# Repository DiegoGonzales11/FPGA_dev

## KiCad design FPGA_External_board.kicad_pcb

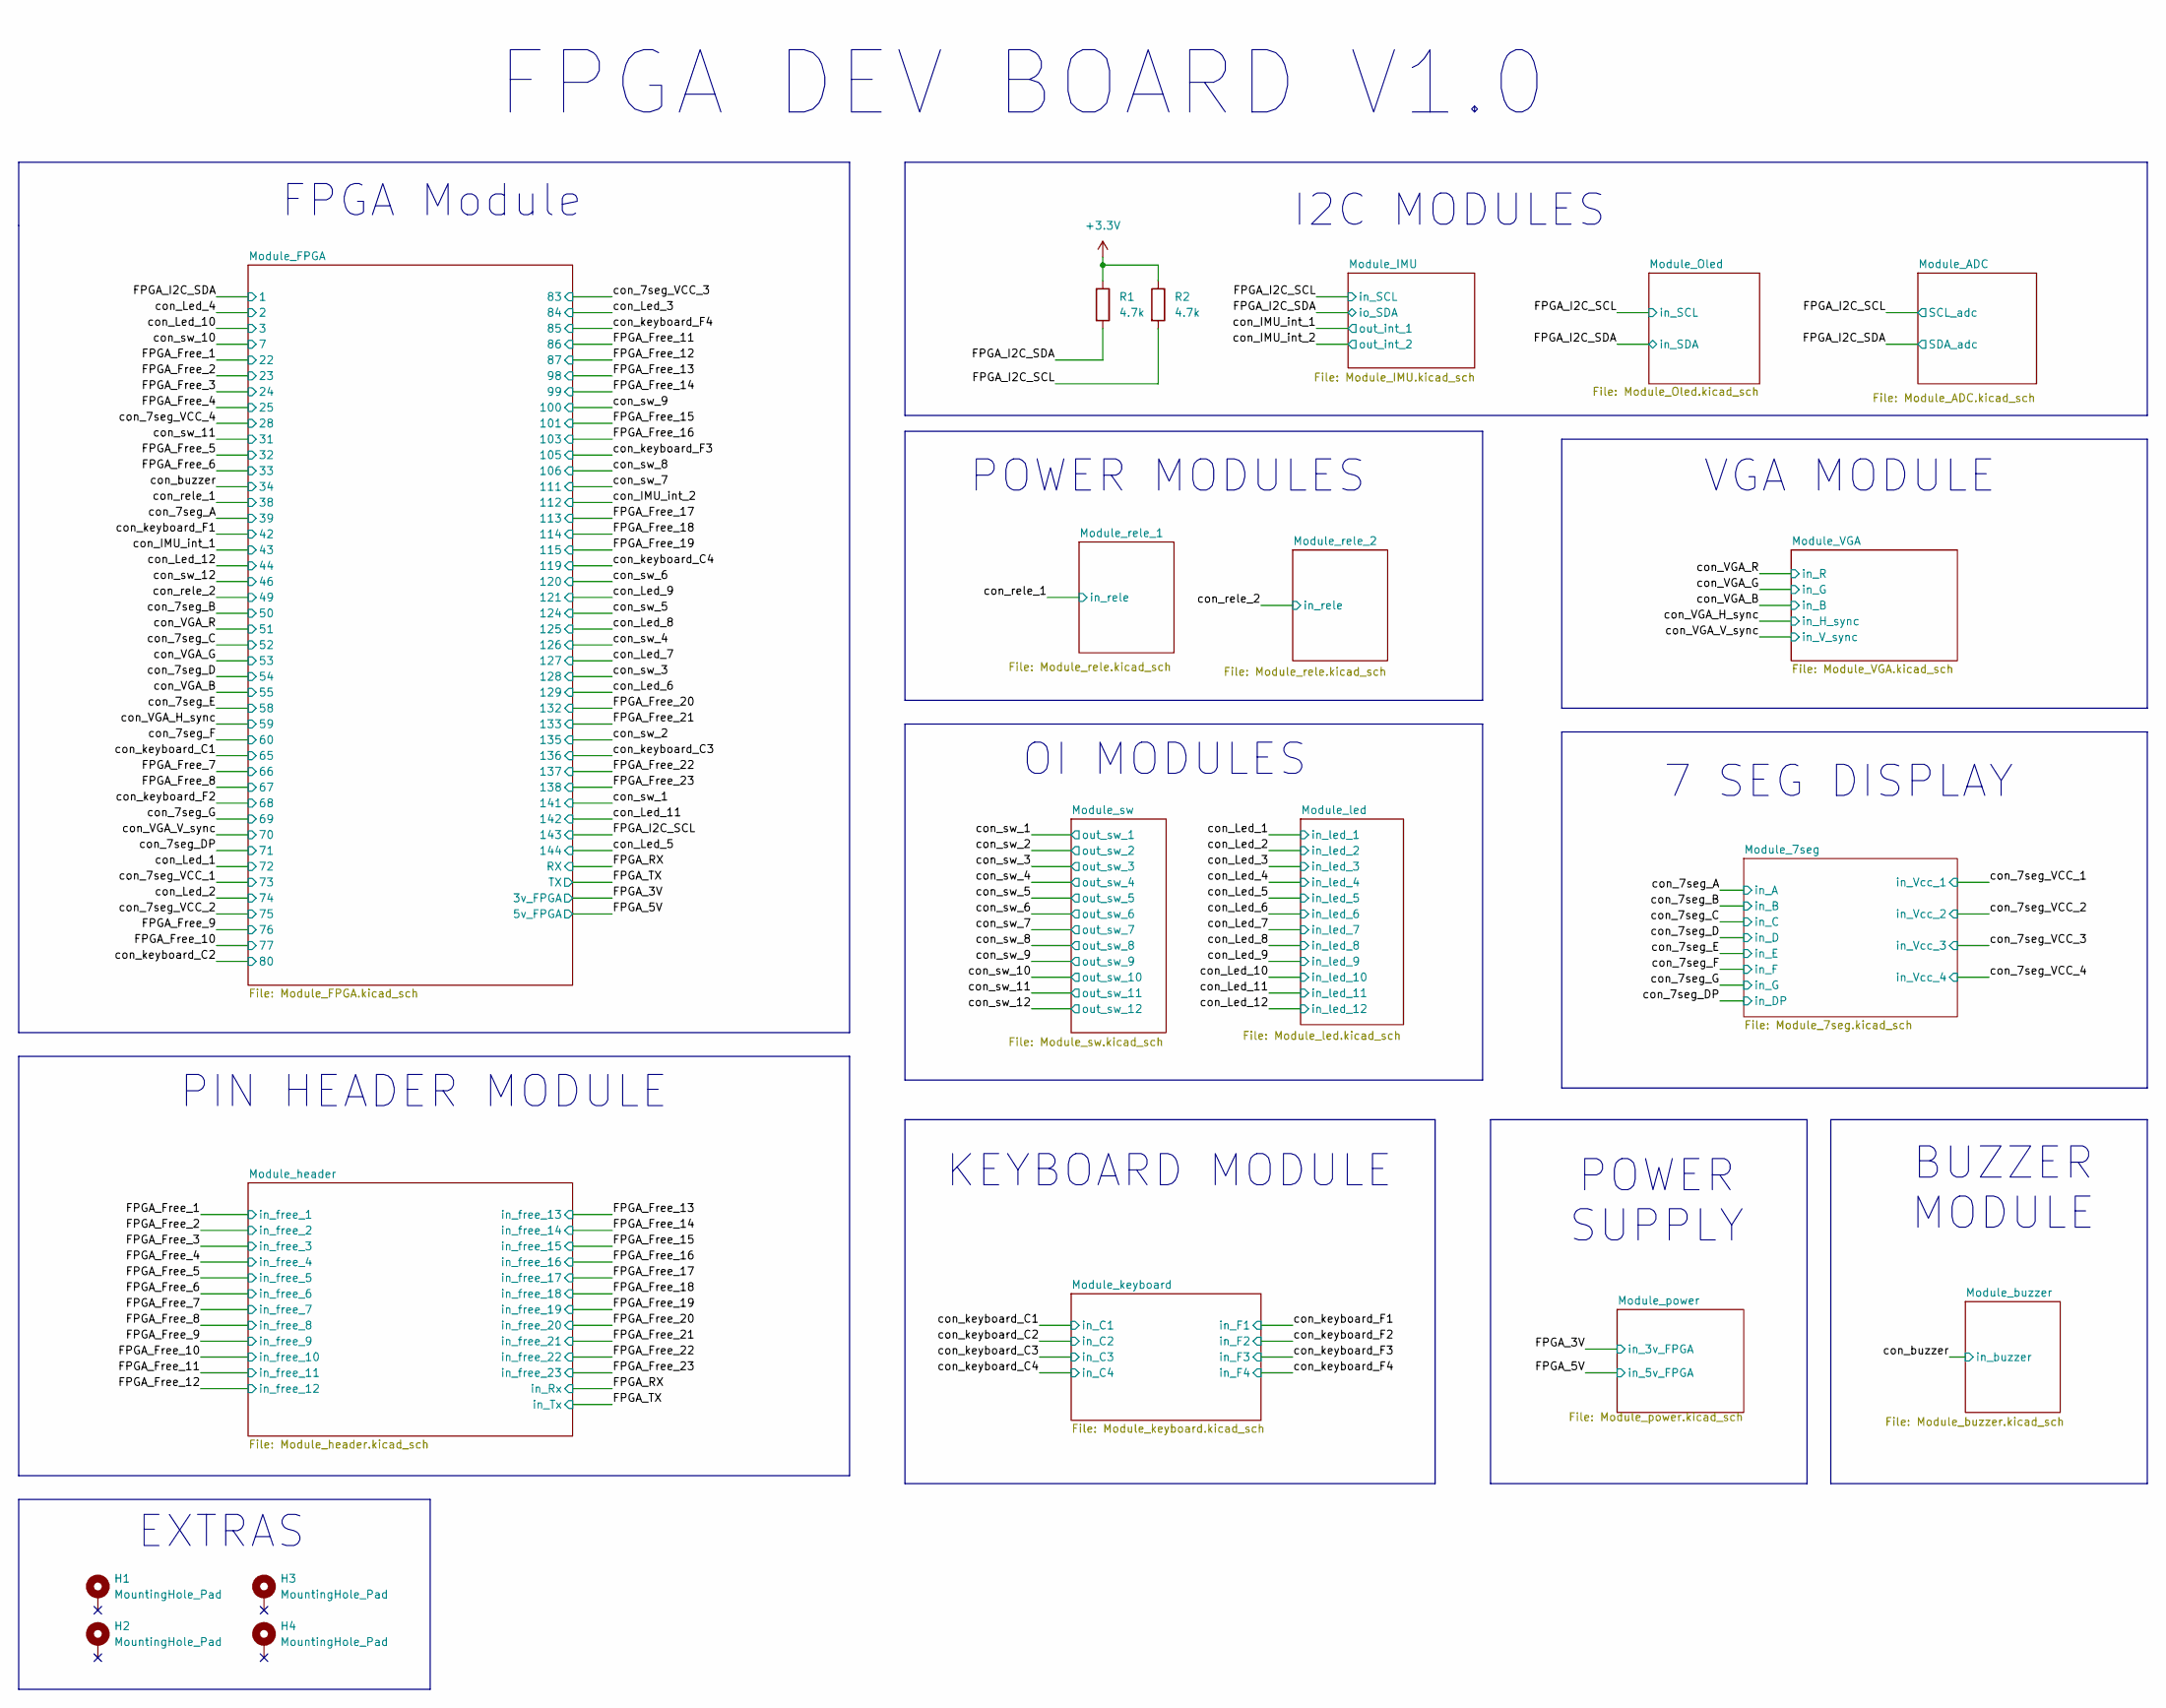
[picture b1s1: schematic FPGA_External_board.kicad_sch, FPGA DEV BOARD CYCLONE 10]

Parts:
H1, H2, H3, H4: MountingHole_Pad; Mounting Hole 3mm
R1, R2: 4.7k; R_0805_2012Metric_Pad1.20x1.40mm_HandSolder

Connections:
+3.3V: R1.1, R2.1; also elsewhere on the board
/FPGA_I2C_SCL: R2.2; also elsewhere on the board
/FPGA_I2C_SDA: R1.2; also elsewhere on the board

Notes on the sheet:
7 SEG DISPLAY
FPGA DEV BOARD V1.0
POWER MODULES
KEYBOARD MODULE
EXTRAS
PIN HEADER MODULE
OI MODULES
FPGA Module
POWER SUPPLY
I2C MODULES
BUZZER MODULE
VGA MODULE

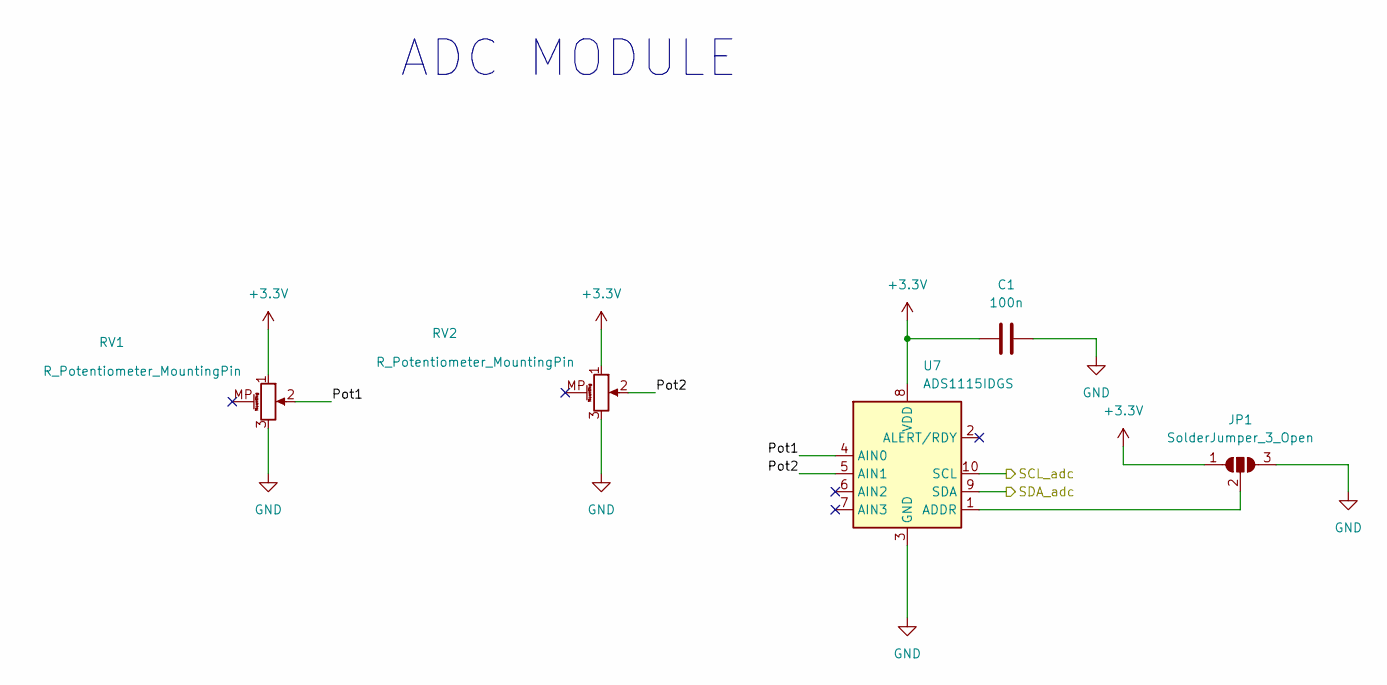
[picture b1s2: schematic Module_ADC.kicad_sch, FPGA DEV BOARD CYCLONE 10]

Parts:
C1: 100n; C_0805_2012Metric
JP1: SolderJumper_3_Open; SolderJumper-3_P1.3mm_Open_RoundedPad1.0x1.5mm
RV1, RV2: R_Potentiometer_MountingPin; Potentiometer_Alps_RK09K_Single_Vertical
U7: ADS1115IDGS; TSSOP-10_3x3mm_P0.5mm

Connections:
+3.3V: C1.2, JP1.1 (A), RV1.1, RV2.1, U7.8 (VDD); also elsewhere on the board
/FPGA_I2C_SCL: U7.10 (SCL); also elsewhere on the board
/FPGA_I2C_SDA: U7.9 (SDA); also elsewhere on the board
/Module_ADC/Pot1: RV1.2, U7.4 (AIN0)
/Module_ADC/Pot2: RV2.2, U7.5 (AIN1)
GND: C1.1, JP1.3 (B), RV1.3, RV2.3, U7.3 (GND); also elsewhere on the board
unnamed: JP1.2 (C), U7.1 (ADDR)

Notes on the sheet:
ADC MODULE

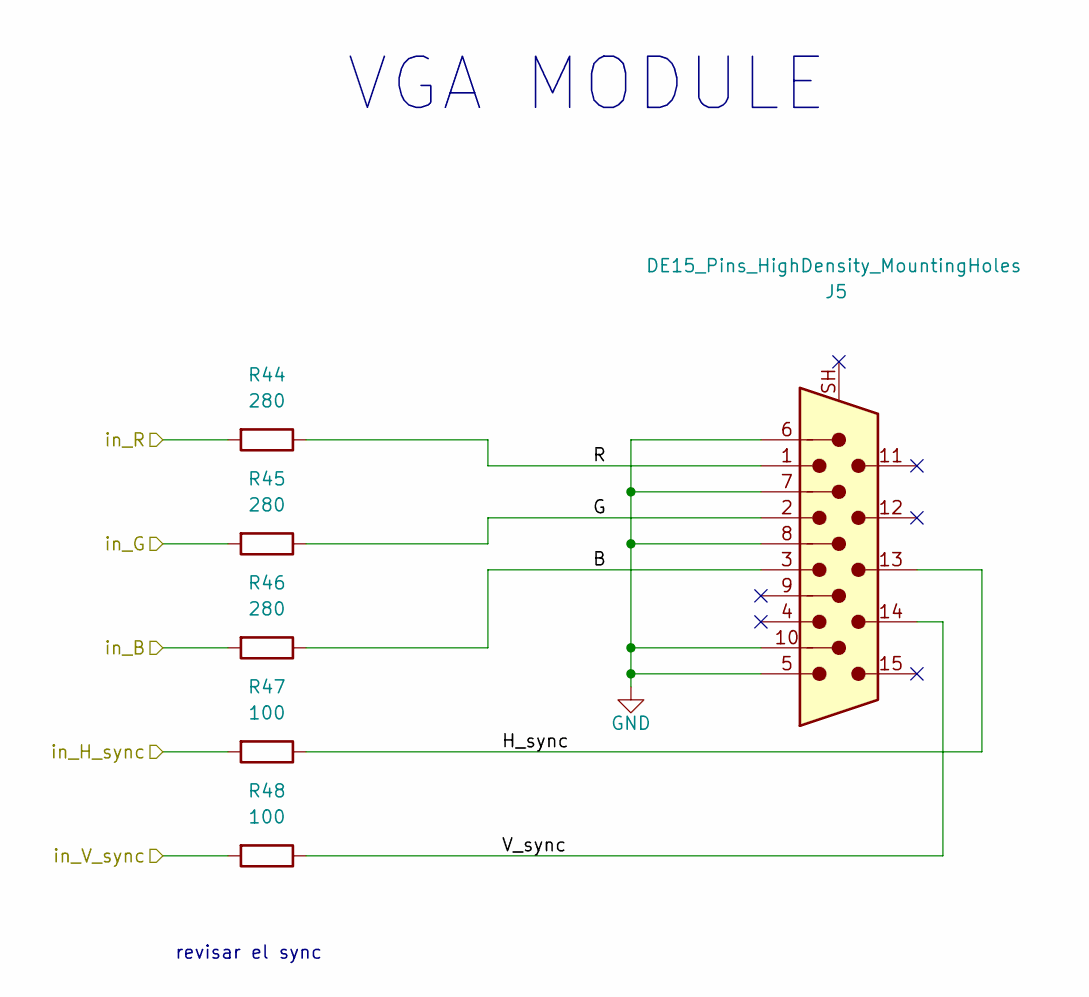
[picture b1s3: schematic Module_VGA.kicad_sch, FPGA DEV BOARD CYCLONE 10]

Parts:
J5: DE15_Pins_HighDensity_MountingHoles; DSUB-15-HD_Pins_Horizontal_P2.29x2.54mm_EdgePinOffset8.35mm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
R44, R45, R46: 280; R_0805_2012Metric_Pad1.20x1.40mm_HandSolder
R47, R48: 100; R_0805_2012Metric_Pad1.20x1.40mm_HandSolder

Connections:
/Module_VGA/B: J5.3, R46.1
/Module_VGA/G: J5.2, R45.1
/Module_VGA/H_sync: J5.13, R47.1
/Module_VGA/R: J5.1, R44.1
/Module_VGA/V_sync: J5.14, R48.1
/con_VGA_B: R46.2; also elsewhere on the board
/con_VGA_G: R45.2; also elsewhere on the board
/con_VGA_H_sync: R47.2; also elsewhere on the board
/con_VGA_R: R44.2; also elsewhere on the board
/con_VGA_V_sync: R48.2; also elsewhere on the board
GND: J5.5, J5.6, J5.7, J5.8, J5.10; also elsewhere on the board

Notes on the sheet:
VGA MODULE
revisar el sync

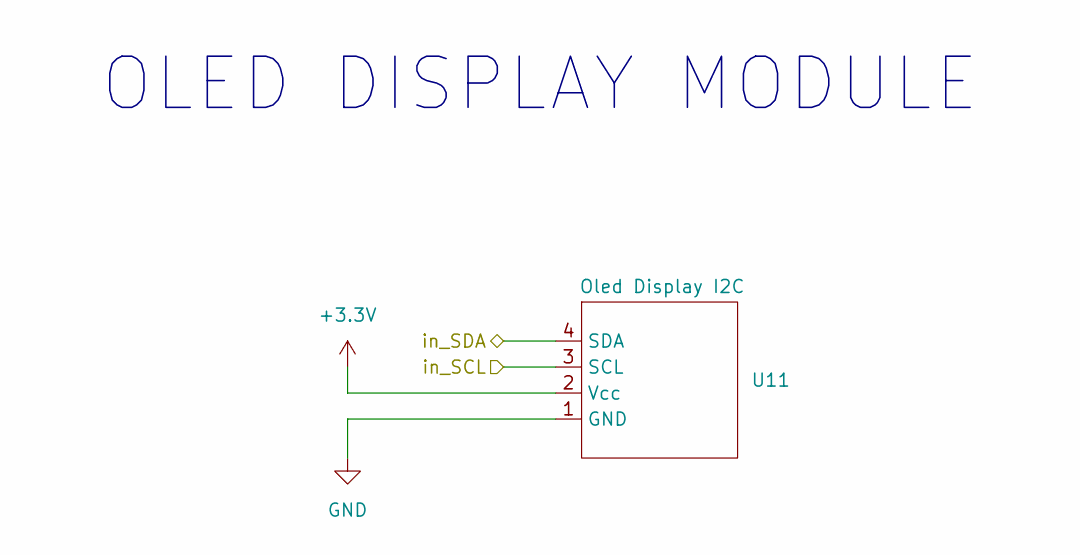
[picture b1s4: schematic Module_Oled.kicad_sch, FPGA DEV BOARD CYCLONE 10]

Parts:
U11: Oled Display I2C; display oled i2c

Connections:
+3.3V: U11.2 (Vcc); also elsewhere on the board
/FPGA_I2C_SCL: U11.3 (SCL); also elsewhere on the board
/FPGA_I2C_SDA: U11.4 (SDA); also elsewhere on the board
GND: U11.1 (GND); also elsewhere on the board

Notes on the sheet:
OLED DISPLAY MODULE

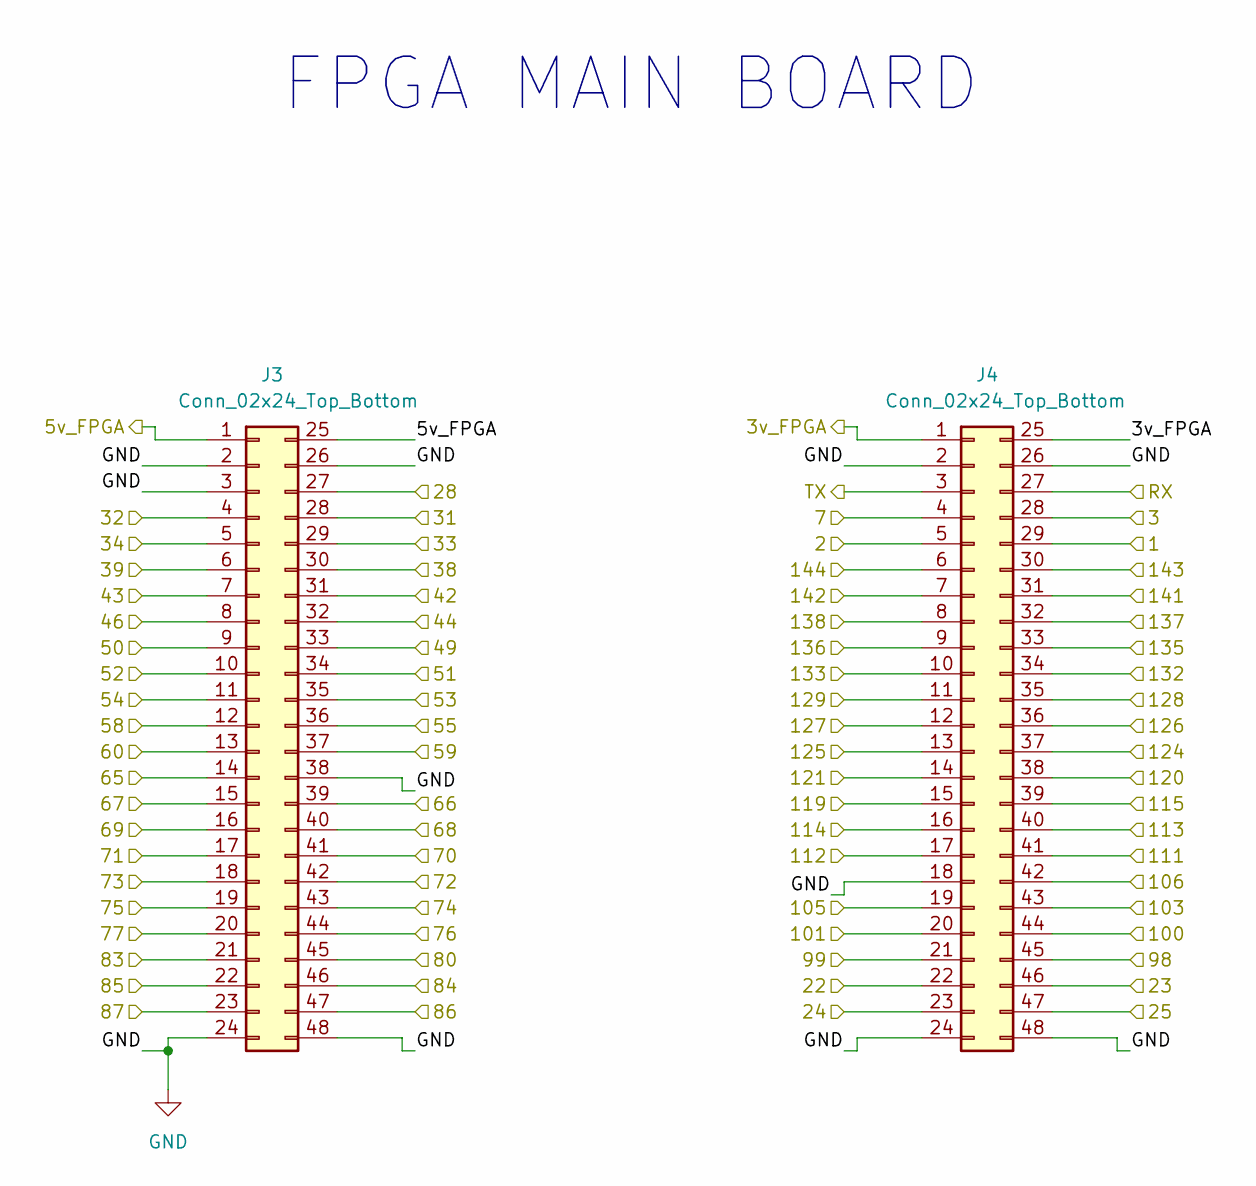
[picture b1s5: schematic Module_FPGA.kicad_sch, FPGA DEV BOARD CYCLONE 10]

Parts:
J3, J4: Conn_02x24_Top_Bottom; Pin header socket 2.54mm 2x24

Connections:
/FPGA_3V: J4.1, J4.25; also elsewhere on the board
/FPGA_5V: J3.1, J3.25; also elsewhere on the board
/FPGA_Free_1: J4.22; also elsewhere on the board
/FPGA_Free_2: J4.46; also elsewhere on the board
/FPGA_Free_3: J4.23; also elsewhere on the board
/FPGA_Free_4: J4.47; also elsewhere on the board
/FPGA_Free_5: J3.4; also elsewhere on the board
/FPGA_Free_6: J3.29; also elsewhere on the board
/FPGA_Free_7: J3.39; also elsewhere on the board
/FPGA_Free_8: J3.15; also elsewhere on the board
/FPGA_Free_9: J3.44; also elsewhere on the board
/FPGA_Free_10: J3.20; also elsewhere on the board
/FPGA_Free_11: J3.47; also elsewhere on the board
/FPGA_Free_12: J3.23; also elsewhere on the board
/FPGA_Free_13: J4.45; also elsewhere on the board
/FPGA_Free_14: J4.21; also elsewhere on the board
/FPGA_Free_15: J4.20; also elsewhere on the board
/FPGA_Free_16: J4.43; also elsewhere on the board
/FPGA_Free_17: J4.40; also elsewhere on the board
/FPGA_Free_18: J4.16; also elsewhere on the board
/FPGA_Free_19: J4.39; also elsewhere on the board
/FPGA_Free_20: J4.34; also elsewhere on the board
/FPGA_Free_21: J4.10; also elsewhere on the board
/FPGA_Free_22: J4.32; also elsewhere on the board
/FPGA_Free_23: J4.8; also elsewhere on the board
/FPGA_I2C_SCL: J4.30; also elsewhere on the board
/FPGA_I2C_SDA: J4.29; also elsewhere on the board
/FPGA_RX: J4.27; also elsewhere on the board
/FPGA_TX: J4.3; also elsewhere on the board
/con_7seg_A: J3.6; also elsewhere on the board
/con_7seg_B: J3.9; also elsewhere on the board
/con_7seg_C: J3.10; also elsewhere on the board
/con_7seg_D: J3.11; also elsewhere on the board
/con_7seg_DP: J3.17; also elsewhere on the board
/con_7seg_E: J3.12; also elsewhere on the board
/con_7seg_F: J3.13; also elsewhere on the board
/con_7seg_G: J3.16; also elsewhere on the board
/con_7seg_VCC_1: J3.18; also elsewhere on the board
/con_7seg_VCC_2: J3.19; also elsewhere on the board
/con_7seg_VCC_3: J3.21; also elsewhere on the board
/con_7seg_VCC_4: J3.27; also elsewhere on the board
/con_IMU_int_1: J3.7; also elsewhere on the board
/con_IMU_int_2: J4.17; also elsewhere on the board
/con_Led_1: J3.42; also elsewhere on the board
/con_Led_2: J3.43; also elsewhere on the board
/con_Led_3: J3.46; also elsewhere on the board
/con_Led_4: J4.5; also elsewhere on the board
/con_Led_5: J4.6; also elsewhere on the board
/con_Led_6: J4.11; also elsewhere on the board
/con_Led_7: J4.12; also elsewhere on the board
/con_Led_8: J4.13; also elsewhere on the board
/con_Led_9: J4.14; also elsewhere on the board
/con_Led_10: J4.28; also elsewhere on the board
/con_Led_11: J4.7; also elsewhere on the board
/con_Led_12: J3.32; also elsewhere on the board
/con_VGA_B: J3.36; also elsewhere on the board
/con_VGA_G: J3.35; also elsewhere on the board
/con_VGA_H_sync: J3.37; also elsewhere on the board
/con_VGA_R: J3.34; also elsewhere on the board
/con_VGA_V_sync: J3.41; also elsewhere on the board
/con_buzzer: J3.5; also elsewhere on the board
/con_keyboard_C1: J3.14; also elsewhere on the board
/con_keyboard_C2: J3.45; also elsewhere on the board
/con_keyboard_C3: J4.9; also elsewhere on the board
/con_keyboard_C4: J4.15; also elsewhere on the board
/con_keyboard_F1: J3.31; also elsewhere on the board
/con_keyboard_F2: J3.40; also elsewhere on the board
/con_keyboard_F3: J4.19; also elsewhere on the board
/con_keyboard_F4: J3.22; also elsewhere on the board
/con_rele_1: J3.30; also elsewhere on the board
/con_rele_2: J3.33; also elsewhere on the board
/con_sw_1: J4.31; also elsewhere on the board
/con_sw_2: J4.33; also elsewhere on the board
/con_sw_3: J4.35; also elsewhere on the board
/con_sw_4: J4.36; also elsewhere on the board
/con_sw_5: J4.37; also elsewhere on the board
/con_sw_6: J4.38; also elsewhere on the board
/con_sw_7: J4.41; also elsewhere on the board
/con_sw_8: J4.42; also elsewhere on the board
/con_sw_9: J4.44; also elsewhere on the board
/con_sw_10: J4.4; also elsewhere on the board
/con_sw_11: J3.28; also elsewhere on the board
/con_sw_12: J3.8; also elsewhere on the board
GND: J3.2, J3.3, J3.24, J3.26, J3.38, J3.48, J4.2, J4.18, J4.24, J4.26, J4.48; also elsewhere on the board

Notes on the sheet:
FPGA MAIN BOARD

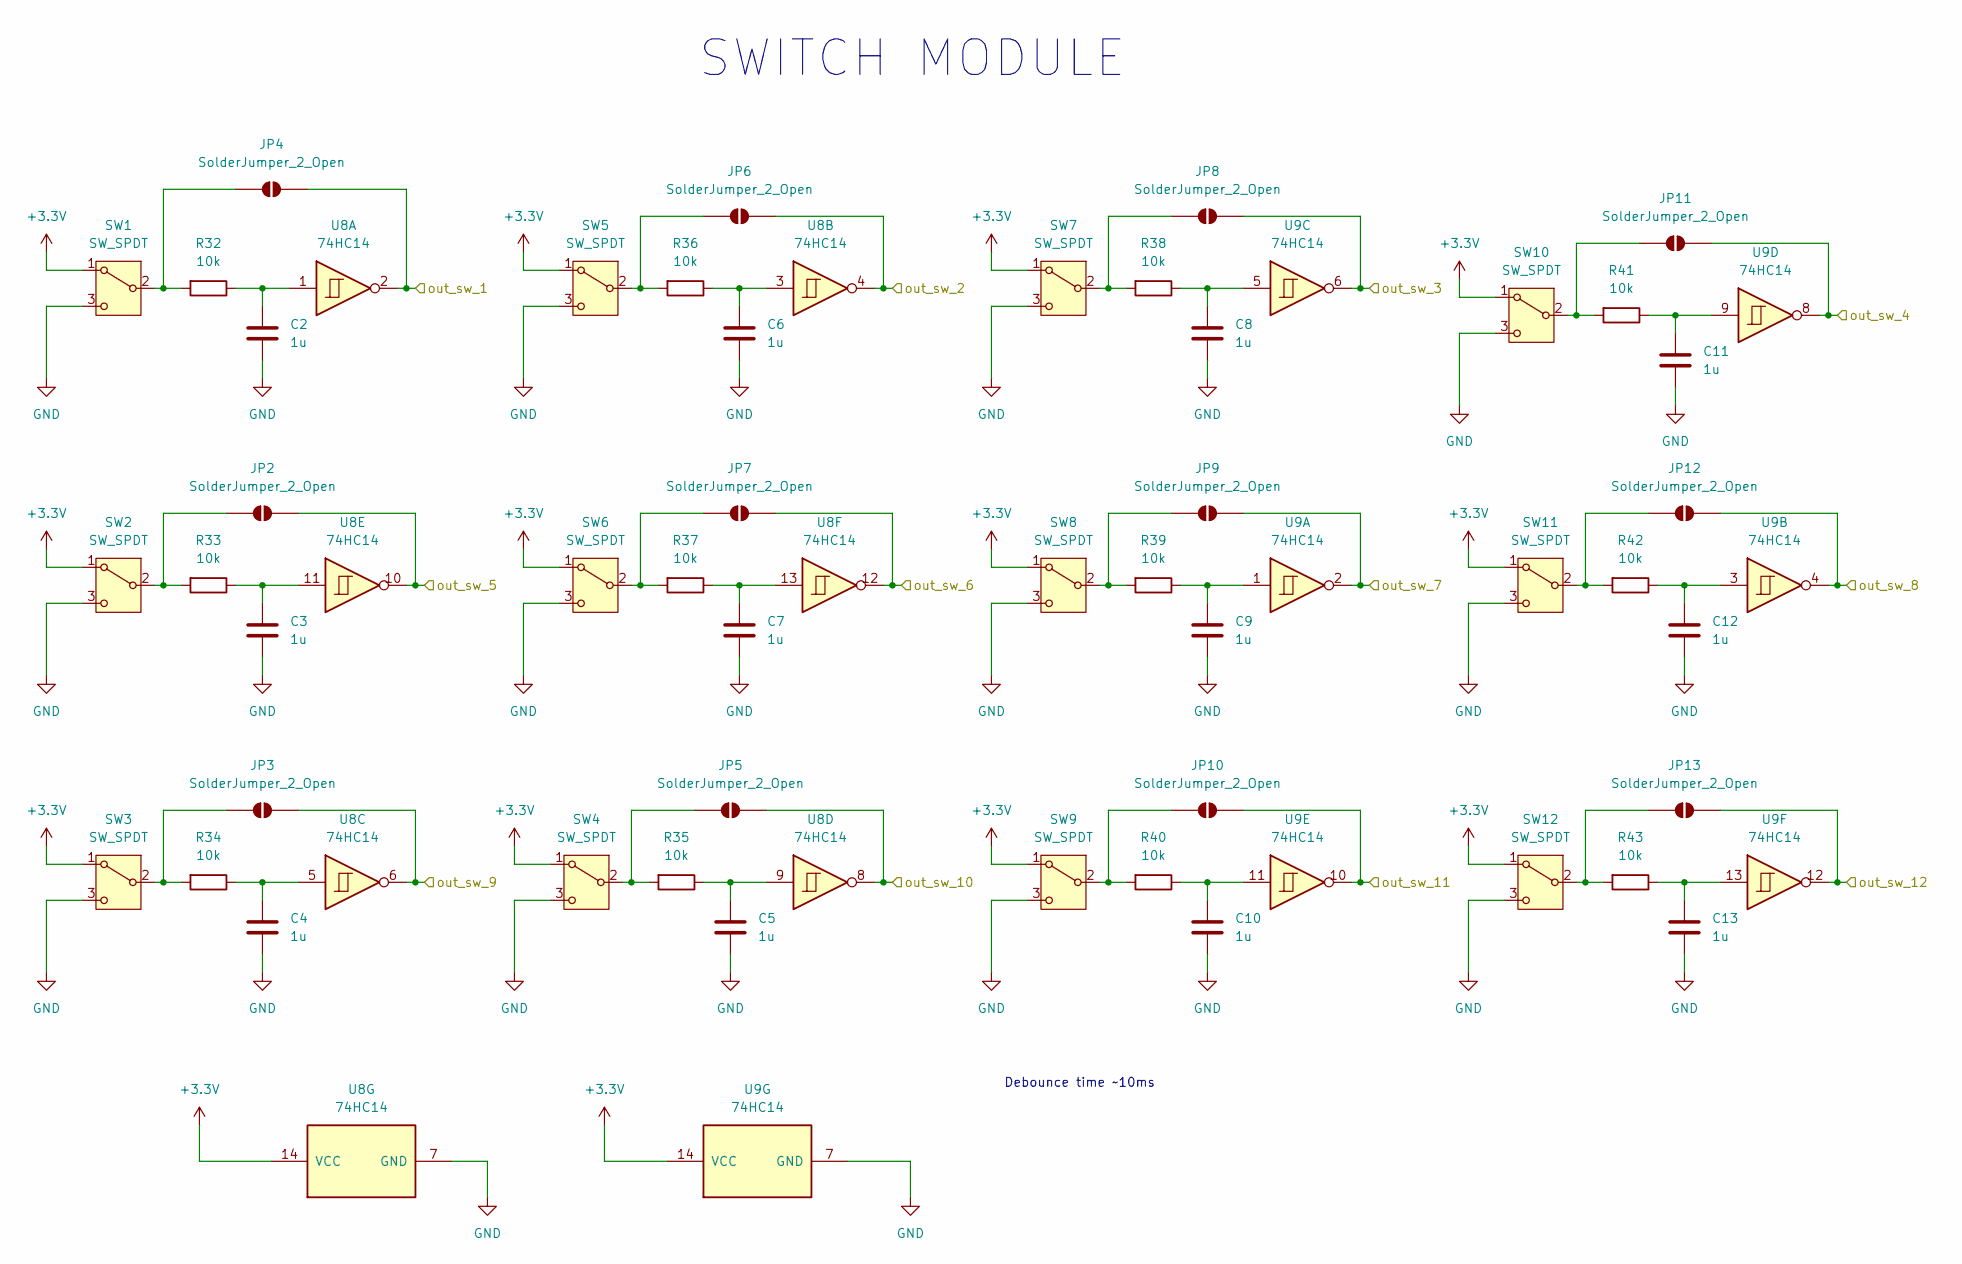
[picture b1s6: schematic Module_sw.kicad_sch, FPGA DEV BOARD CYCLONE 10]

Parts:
C2, C3, C4, C5, C6, C7, C8, C9, C10, C11, C12, C13: 1u; C_0805_2012Metric
JP2, JP3, JP4, JP5, JP6, JP7, JP8, JP9, JP10, JP11, JP12, JP13: SolderJumper_2_Open; SolderJumper-2_P1.3mm_Open_RoundedPad1.0x1.5mm
R32, R33, R34, R35, R36, R37, R38, R39, R40, R41, R42, R43: 10k; R_0805_2012Metric_Pad1.20x1.40mm_HandSolder
SW1, SW2, SW3, SW4, SW5, SW6, SW7, SW8, SW9, SW10, SW11, SW12: SW_SPDT; SW_Slide_SPDT_Straight_CK_OS102011MS2Q
U8, U9: 74HC14; SO-14_3.9x8.65mm_P1.27mm

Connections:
+3.3V: SW1.1 (A), SW2.1 (A), SW3.1 (A), SW4.1 (A), SW5.1 (A), SW6.1 (A), SW7.1 (A), SW8.1 (A), SW9.1 (A), SW10.1 (A), SW11.1 (A), SW12.1 (A), U8.14 (VCC), U9.14 (VCC); also elsewhere on the board
/con_sw_1: JP4.2 (B), U8.2; also elsewhere on the board
/con_sw_2: JP6.2 (B), U8.4; also elsewhere on the board
/con_sw_3: JP8.2 (B), U9.6; also elsewhere on the board
/con_sw_4: JP11.2 (B), U9.8; also elsewhere on the board
/con_sw_5: JP2.2 (B), U8.10; also elsewhere on the board
/con_sw_6: JP7.2 (B), U8.12; also elsewhere on the board
/con_sw_7: JP9.2 (B), U9.2; also elsewhere on the board
/con_sw_8: JP12.2 (B), U9.4; also elsewhere on the board
/con_sw_9: JP3.2 (B), U8.6; also elsewhere on the board
/con_sw_10: JP5.2 (B), U8.8; also elsewhere on the board
/con_sw_11: JP10.2 (B), U9.10; also elsewhere on the board
/con_sw_12: JP13.2 (B), U9.12; also elsewhere on the board
GND: C2.2, C3.2, C4.2, C5.2, C6.2, C7.2, C8.2, C9.2, C10.2, C11.2, C12.2, C13.2, SW1.3 (C), SW2.3 (C), SW3.3 (C), SW4.3 (C), SW5.3 (C), SW6.3 (C), SW7.3 (C), SW8.3 (C), SW9.3 (C), SW10.3 (C), SW11.3 (C), SW12.3 (C), U8.7 (GND), U9.7 (GND); also elsewhere on the board
unnamed: C2.1, R32.1, U8.1
unnamed: C3.1, R33.1, U8.11
unnamed: C4.1, R34.1, U8.5
unnamed: C5.1, R35.1, U8.9
unnamed: C6.1, R36.1, U8.3
unnamed: C7.1, R37.1, U8.13
unnamed: C8.1, R38.1, U9.5
unnamed: C9.1, R39.1, U9.1
unnamed: C10.1, R40.1, U9.11
unnamed: C11.1, R41.1, U9.9
unnamed: C12.1, R42.1, U9.3
unnamed: C13.1, R43.1, U9.13
unnamed: JP2.1 (A), R33.2, SW2.2 (B)
unnamed: JP3.1 (A), R34.2, SW3.2 (B)
unnamed: JP4.1 (A), R32.2, SW1.2 (B)
unnamed: JP5.1 (A), R35.2, SW4.2 (B)
unnamed: JP6.1 (A), R36.2, SW5.2 (B)
unnamed: JP7.1 (A), R37.2, SW6.2 (B)
unnamed: JP8.1 (A), R38.2, SW7.2 (B)
unnamed: JP9.1 (A), R39.2, SW8.2 (B)
unnamed: JP10.1 (A), R40.2, SW9.2 (B)
unnamed: JP11.1 (A), R41.2, SW10.2 (B)
unnamed: JP12.1 (A), R42.2, SW11.2 (B)
unnamed: JP13.1 (A), R43.2, SW12.2 (B)

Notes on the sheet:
Debounce time ~10ms
SWITCH MODULE

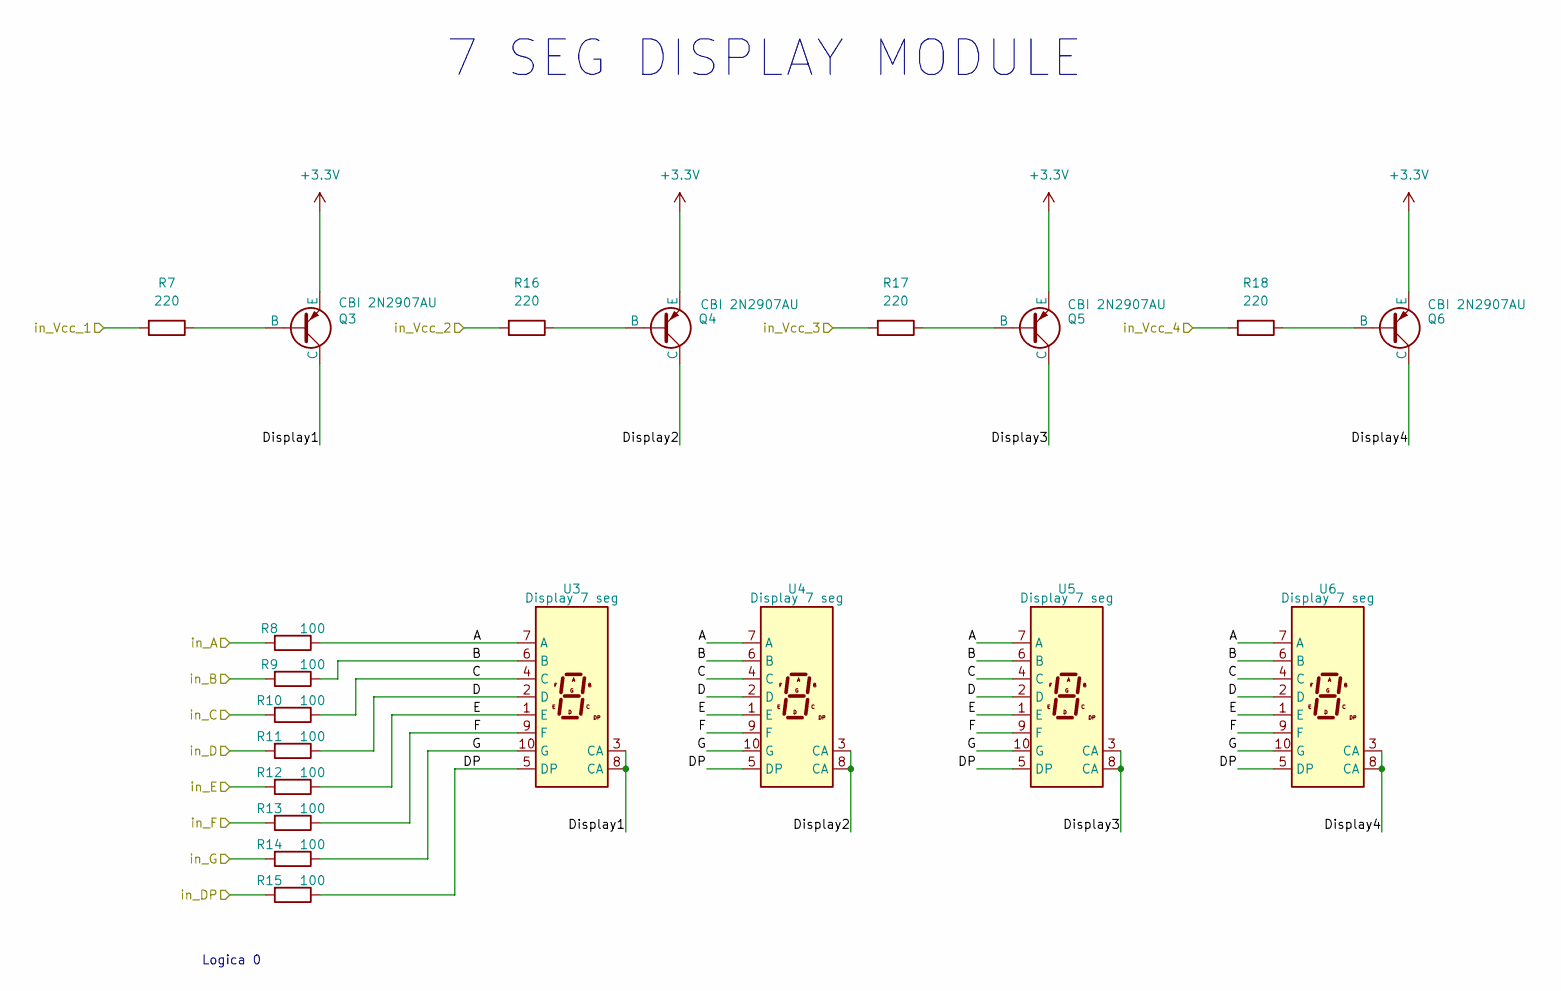
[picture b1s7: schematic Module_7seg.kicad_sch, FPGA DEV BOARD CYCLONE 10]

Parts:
Q3, Q4, Q5, Q6: CBI 2N2907AU; Transistor PNP 2N2907AU - SOT-89
R7, R16, R17, R18: 220; R_0805_2012Metric_Pad1.20x1.40mm_HandSolder
R8, R9, R10, R11, R12, R13, R14, R15: 100; R_0805_2012Metric_Pad1.20x1.40mm_HandSolder
U3, U4, U5, U6: Display 7 seg; 7SegmentLED_LTS6760_LTS6780

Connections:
+3.3V: Q3.3 (E), Q4.3 (E), Q5.3 (E), Q6.3 (E); also elsewhere on the board
/Module_7seg/A: R8.1, U3.7 (A), U4.7 (A), U5.7 (A), U6.7 (A)
/Module_7seg/B: R9.1, U3.6 (B), U4.6 (B), U5.6 (B), U6.6 (B)
/Module_7seg/C: R10.1, U3.4 (C), U4.4 (C), U5.4 (C), U6.4 (C)
/Module_7seg/D: R11.1, U3.2 (D), U4.2 (D), U5.2 (D), U6.2 (D)
/Module_7seg/DP: R15.1, U3.5 (DP), U4.5 (DP), U5.5 (DP), U6.5 (DP)
/Module_7seg/Display1: Q3.1 (C), U3.3 (CA), U3.8 (CA)
/Module_7seg/Display2: Q4.1 (C), U4.3 (CA), U4.8 (CA)
/Module_7seg/Display3: Q5.1 (C), U5.3 (CA), U5.8 (CA)
/Module_7seg/Display4: Q6.1 (C), U6.3 (CA), U6.8 (CA)
/Module_7seg/E: R12.1, U3.1 (E), U4.1 (E), U5.1 (E), U6.1 (E)
/Module_7seg/F: R13.1, U3.9 (F), U4.9 (F), U5.9 (F), U6.9 (F)
/Module_7seg/G: R14.1, U3.10 (G), U4.10 (G), U5.10 (G), U6.10 (G)
/con_7seg_A: R8.2; also elsewhere on the board
/con_7seg_B: R9.2; also elsewhere on the board
/con_7seg_C: R10.2; also elsewhere on the board
/con_7seg_D: R11.2; also elsewhere on the board
/con_7seg_DP: R15.2; also elsewhere on the board
/con_7seg_E: R12.2; also elsewhere on the board
/con_7seg_F: R13.2; also elsewhere on the board
/con_7seg_G: R14.2; also elsewhere on the board
/con_7seg_VCC_1: R7.2; also elsewhere on the board
/con_7seg_VCC_2: R16.2; also elsewhere on the board
/con_7seg_VCC_3: R17.2; also elsewhere on the board
/con_7seg_VCC_4: R18.2; also elsewhere on the board
unnamed: Q3.2 (B), R7.1
unnamed: Q4.2 (B), R16.1
unnamed: Q5.2 (B), R17.1
unnamed: Q6.2 (B), R18.1

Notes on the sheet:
Logica 0
7 SEG DISPLAY MODULE

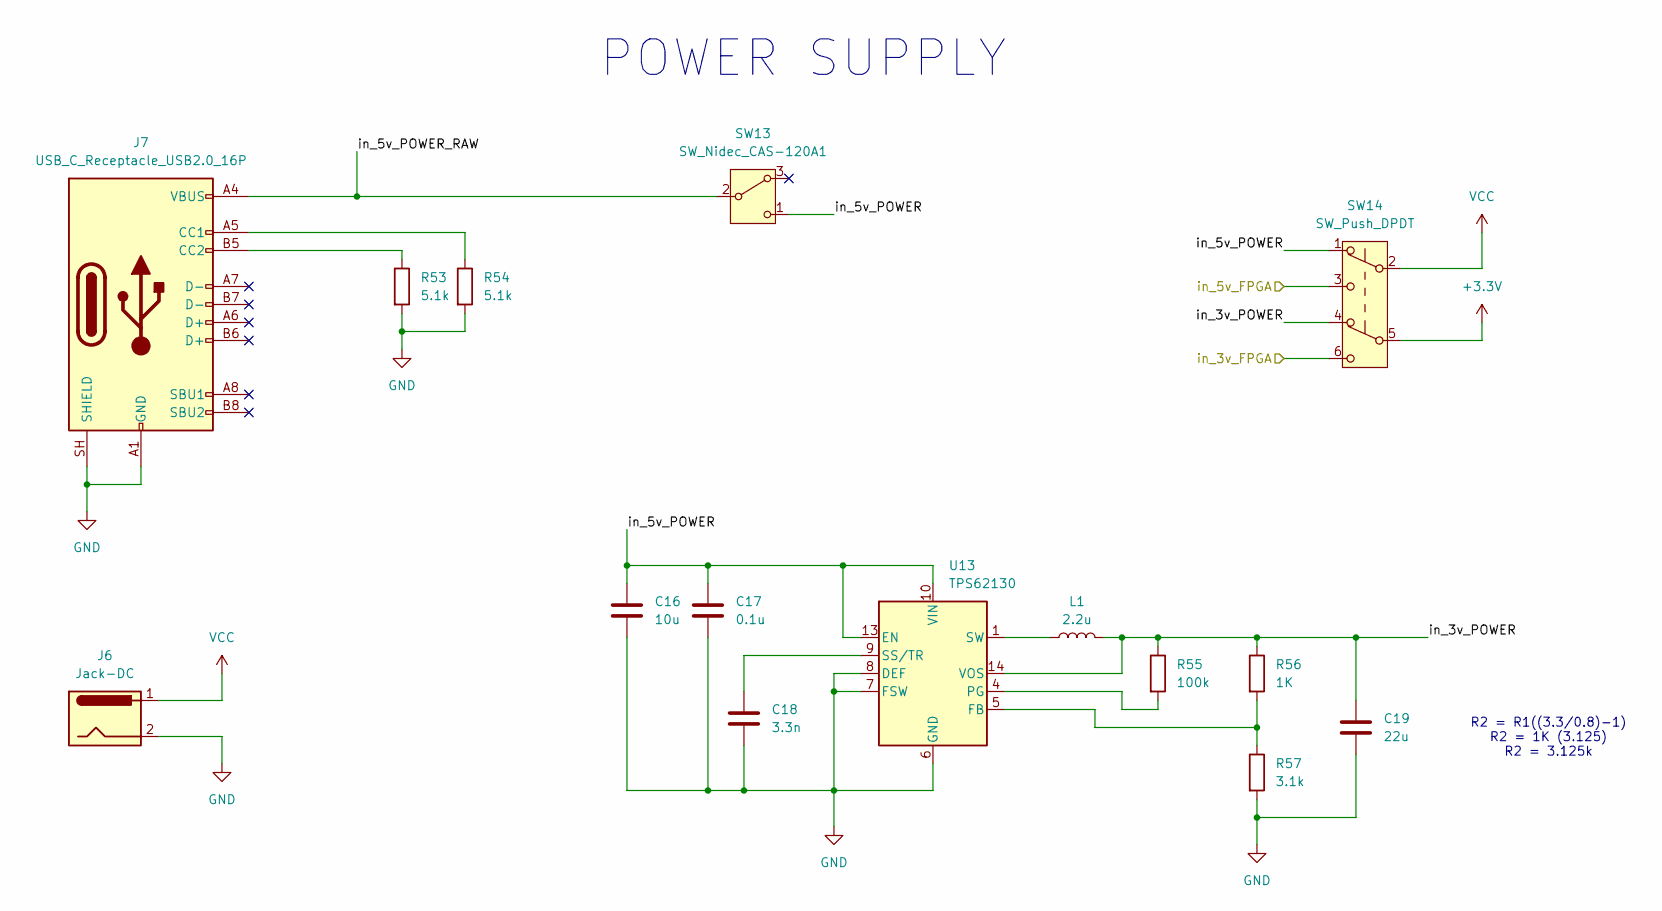
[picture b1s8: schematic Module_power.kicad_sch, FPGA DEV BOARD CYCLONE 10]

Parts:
C16: 10u; C_0805_2012Metric
C17: 0.1u; C_0805_2012Metric
C18: 3.3n; C_0805_2012Metric
C19: 22u; C_0805_2012Metric
J6: Jack-DC; BarrelJack_Kycon_KLDX-0202-xC_Horizontal
J7: USB_C_Receptacle_USB2.0_16P; USB_C_Receptacle_GCT_USB4105-xx-A_16P_TopMnt_Horizontal
L1: 2.2u; L_Changjiang_FXL0420
R53, R54: 5.1k; R_0805_2012Metric_Pad1.20x1.40mm_HandSolder
R55: 100k; R_0805_2012Metric_Pad1.20x1.40mm_HandSolder
R56: 1K; R_0805_2012Metric_Pad1.20x1.40mm_HandSolder
R57: 3.1k; R_0805_2012Metric_Pad1.20x1.40mm_HandSolder
SW13: SW_Nidec_CAS-120A1; Switch Dailywell P3
SW14: SW_Push_DPDT; Switch Dailywell P6
U13: TPS62130; VQFN-16-1EP_3x3mm_P0.5mm_EP1.68x1.68mm_ThermalVias

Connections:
+3.3V: SW14.5 (B); also elsewhere on the board
/FPGA_3V: SW14.6 (C); also elsewhere on the board
/FPGA_5V: SW14.3 (C); also elsewhere on the board
/Module_power/in_3v_POWER: C19.1, L1.2, R55.1, R56.1, SW14.4 (A), U13.14 (VOS)
/Module_power/in_5v_POWER: C16.1, C17.1, SW13.1 (C), SW14.1 (A), U13.10 (VIN), U13.11 (VIN), U13.12 (VIN), U13.13 (EN)
/Module_power/in_5v_POWER_RAW: J7.A4 (VBUS), J7.A9 (VBUS), J7.B4 (VBUS), J7.B9 (VBUS), SW13.2 (B)
GND: C16.2, C17.2, C18.2, C19.2, J6.2, J7.A1 (GND), J7.A12 (GND), J7.B1 (GND), J7.B12 (GND), J7.SH (SHIELD), R53.2, R54.2, R57.2, U13.6 (GND), U13.7 (FSW), U13.8 (DEF), U13.15 (GND), U13.16 (GND), U13.17 (GND); also elsewhere on the board
unnamed: J7.A5 (CC1), R54.1
unnamed: J7.B5 (CC2), R53.1
unnamed: L1.1, U13.1 (SW), U13.2 (SW), U13.3 (SW)
unnamed: R56.2, R57.1, U13.5 (FB)
unnamed: R55.2, U13.4 (PG)
unnamed: C18.1, U13.9 (SS/TR)
VCC: J6.1, SW14.2 (B); also elsewhere on the board

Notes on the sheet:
POWER SUPPLY
R2 = R1((3.3/0.8)-1) R2 = 1K (3.125) R2 = 3.125k

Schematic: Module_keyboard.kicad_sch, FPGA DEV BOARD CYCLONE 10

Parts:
R49, R50, R51, R52: 10K; R_0805_2012Metric_Pad1.20x1.40mm_HandSolder
U12: Keyboard 4x4

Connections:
+3.3V: R49.1, R50.1, R51.1, R52.1; also elsewhere on the board
/con_keyboard_C1: R49.2, U12.8 (C4); also elsewhere on the board
/con_keyboard_C2: R50.2, U12.7 (C3); also elsewhere on the board
/con_keyboard_C3: R51.2, U12.6 (C2); also elsewhere on the board
/con_keyboard_C4: R52.2, U12.5 (C1); also elsewhere on the board
/con_keyboard_F1: U12.1 (F1); also elsewhere on the board
/con_keyboard_F2: U12.2 (F2); also elsewhere on the board
/con_keyboard_F3: U12.3 (F3); also elsewhere on the board
/con_keyboard_F4: U12.4 (F4); also elsewhere on the board

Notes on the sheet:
KEYBOARD 4X4 MODULE

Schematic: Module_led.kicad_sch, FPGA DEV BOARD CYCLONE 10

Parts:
D5, D6, D7, D8, D9, D10, D11, D12, D13, D14, D15, D16: LED; LED_1206_3216Metric_Pad1.42x1.75mm_HandSolder
R20, R21, R22, R23, R24, R25, R26, R27, R28, R29, R30, R31: 300; R_0805_2012Metric_Pad1.20x1.40mm_HandSolder

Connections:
/con_Led_1: R20.1; also elsewhere on the board
/con_Led_2: R21.1; also elsewhere on the board
/con_Led_3: R22.1; also elsewhere on the board
/con_Led_4: R23.1; also elsewhere on the board
/con_Led_5: R24.1; also elsewhere on the board
/con_Led_6: R25.1; also elsewhere on the board
/con_Led_7: R26.1; also elsewhere on the board
/con_Led_8: R27.1; also elsewhere on the board
/con_Led_9: R28.1; also elsewhere on the board
/con_Led_10: R29.1; also elsewhere on the board
/con_Led_11: R30.1; also elsewhere on the board
/con_Led_12: R31.1; also elsewhere on the board
GND: D5.1 (K), D6.1 (K), D7.1 (K), D8.1 (K), D9.1 (K), D10.1 (K), D11.1 (K), D12.1 (K), D13.1 (K), D14.1 (K), D15.1 (K), D16.1 (K); also elsewhere on the board
unnamed: D5.2 (A), R20.2
unnamed: D6.2 (A), R21.2
unnamed: D7.2 (A), R22.2
unnamed: D8.2 (A), R23.2
unnamed: D9.2 (A), R24.2
unnamed: D10.2 (A), R25.2
unnamed: D11.2 (A), R26.2
unnamed: D12.2 (A), R27.2
unnamed: D13.2 (A), R28.2
unnamed: D14.2 (A), R29.2
unnamed: D15.2 (A), R30.2
unnamed: D16.2 (A), R31.2

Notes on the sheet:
LED MODULE
